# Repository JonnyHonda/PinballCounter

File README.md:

# Pinball Counter

An 8-digit decimal score counter built entirely from 74LS-series TTL logic.
Each digit has its own trigger input, so a pinball switch can add 1, 10, 100,
... directly. Digits carry into the next digit like electromechanical score
reels: when a digit goes 9 → 0, it adds 1 to the digit on its left.

## Files

| File | What it is |
|---|---|
| `PinballCounter.sch` | Autodesk EAGLE 9.x schematic (3 sheets, embedded library `pinball_ttl`) |
| `PinballCounter.brd` | EAGLE 9.x board: parts placed, connections as airwires, not yet routed |
| `gen_schematic.py` | Python 3 script that generates the schematic. Edit this, then rerun it; don't hand-edit the `.sch` file if you want to keep regenerating it. |
| `gen_board.py` | Generates the board from the same part and net data, so the schematic and board stay consistent |

Regenerate both with:

```sh
python3 gen_schematic.py && python3 gen_board.py
```

> Once you start routing in EAGLE, the `.brd` file holds your work, so
> rerunning `gen_board.py` would overwrite it. After that point, make
> changes in EAGLE.

The script runs a self-check (every symbol pin maps to a pad, no pad is used
twice, no net has only one connection). It prints any problems before writing
the file.

> **Status:** the schematic has not yet been opened in EAGLE. It parses as
> valid XML and passes the script's self-check, and rendered previews show a
> clean layout. The first step in EAGLE should be an ERC run (see *Known
> ERC warnings*).

## How it works

Signal path for each digit *n* (digit 1 = ones, digit 8 = ten-millions):

```
 Switch ──► 74LS221 one-shot ──► TRIGn ─┐
 (to GND)   (~23 ms, active low)        ├─► 74LS08 AND ─► CLKn ─► CPU  74LS192  Q0-Q3 ─► 74LS47 ─► 330R ×7 ─► 7-seg (CA)
 CARRY(n-1) from digit n-1 ─────────────┘                               /TCU ─► CARRYn (to digit n+1)
```

- **Debounce:** pinball switches bounce. Each input drives the falling-edge
  trigger (`/A`) of a non-retriggerable 74LS221 one-shot. Each one-shot outputs
  a single clean low pulse of width ≈ 0.7 × R × C = 0.7 × 33 kΩ × 1 µF ≈ 23 ms.
- **Trigger and carry merge:** the 74LS192 counts up on the *rising* edge of
  `CPU`. Its carry output `/TCU` is normally HIGH and goes LOW only when the
  count is 9 and `CPU` is low. When `CPU` rises, the counter goes to 0 and
  `/TCU` rises with it. The trigger and the carry both idle HIGH and pulse
  LOW, so ANDing them means either one pulls the clock low, and the return to
  HIGH counts one step.
- **Digit 1** has no carry in, so its AND input B is tied to VCC.
- **Display:** a 74LS47 (open-collector BCD → 7-segment decoder) drives a
  common-anode display through 330 Ω resistors, at about 9 mA per segment.
  There's no multiplexing; every digit is driven continuously.
- **Leading-zero blanking:** digit 8 `/RBI` = GND. Each digit's `/BI/RBO`
  feeds the `/RBI` of the digit below it, and digit 1 `/RBI` = VCC. A score
  of 0 therefore shows a single "0", and 1234 shows as `    1234`.
- **Reset:** the S1 pushbutton (to GND) and a 10 µF / 4.7 kΩ RC give a
  manual reset and a power-on reset. A 74LS14 Schmitt inverter turns this
  into an active-high `RESET` that drives `MR` on all eight 74LS192s.
  (Driving eight LS inputs from a gate avoids needing a very small pull-down
  resistor.)

## Schematic sheets

1. **Inputs, debounce, reset, power:** J1, J2, U19–U22 (74LS221), R1–R16,
   C1–C8, S1, R73, C9, U23 (74LS14), decoupling C10–C33.
2. **Counter chain:** U1–U8 (74LS192, one per digit) and U17–U18 (74LS08).
3. **Decoders and displays:** U9–U16 (74LS47), R17–R72 (segment resistors),
   DS1–DS8.

Connections use short wire stubs with **net labels**. Pins with the same
label are connected, including across sheets.

### Net naming

| Net | Meaning |
|---|---|
| `SWn` | Raw switch input n (J1 pin n, with pull-up) |
| `CXn`, `RCXn` | 74LS221 timing capacitor/resistor nodes for channel n |
| `TRIGn` | Debounced trigger pulse for digit n (active low) |
| `CARRYn` | 74LS192 `/TCU` of digit n → AND gate of digit n+1 |
| `CLKn` | Clock into `CPU` of digit n |
| `Dn_Q0`–`Dn_Q3` | BCD output of digit n |
| `Dn_SEGA`–`G` | 74LS47 output (before resistor) |
| `Dn_LEDA`–`G` | Display segment (after resistor) |
| `RBOn` | Blanking output of digit n → `/RBI` of digit n-1 |
| `RST_N`, `RESET` | Reset button node (active low) / buffered reset (active high) |

## Bill of materials

| Ref | Qty | Part | Notes |
|---|---|---|---|
| U1–U8 | 8 | 74LS192 | BCD up/down counter, DIP-16 |
| U9–U16 | 8 | 74LS47 | BCD → 7-seg decoder/driver, open collector, DIP-16 |
| U17–U18 | 2 | 74LS08 | Quad 2-input AND, DIP-14 |
| U19–U22 | 4 | 74LS221 | Dual monostable, DIP-16 |
| U23 | 1 | 74LS14 | Hex Schmitt inverter, DIP-14 |
| DS1–DS8 | 8 | 0.56" common-anode 7-seg | 5161BS / SA56-11 pinout |
| R1–R8 | 8 | 4.7 kΩ | Switch pull-ups |
| R9–R16 | 8 | 33 kΩ | One-shot timing |
| R17–R72 | 56 | 330 Ω | Segment current limiting |
| R73 | 1 | 4.7 kΩ | Reset pull-up |
| C1–C8 | 8 | 1 µF ceramic | One-shot timing (non-polarised) |
| C9 | 1 | 10 µF electrolytic | Power-on reset, pin 1 = + |
| C10–C32 | 23 | 100 nF ceramic | Decoupling, one per IC |
| C33 | 1 | 100 µF electrolytic | Bulk supply, pin 1 = + |
| S1 | 1 | 6 mm tactile switch | Reset |
| J1 | 1 | 1×10 header | SW1–SW8, GND, GND |
| J2 | 1 | 1×2 header | +5 V, GND |

**Power:** 5 V regulated, at least 1 A. All segments lit draws about 600 mA
for the LEDs plus about 300 mA for the logic.

## Board layout

**Size:** 194.9 × 160 mm, 2 layers, 4 × M3 mounting holes (3.2 mm) in the
corners.

**Arrangement (top view):** one column per digit, with digit 8 on the left
so the score reads normally. Each column, from top to bottom:

1. 7-segment display (with a silkscreen label for its place value: 10 000 000 … 1)
2. Seven 330 Ω segment resistors
3. 74LS47 decoder, then its 100 nF decoupling capacitor
4. 74LS192 counter

The lower part of the board holds the shared logic, from top to bottom:

- **74LS08 row:** two 74LS08s. U18 serves digits 5–8 and U17 serves digits
  1–4.
- **74LS221 row:** four 74LS221s, each under the two digits it serves.
- **R/C row:** each digit's pull-up, timing resistor and timing capacitor,
  standing vertically under its 74LS221.
- **Bottom edge:** J2 (+5 V / GND), C33 bulk capacitor, S1 reset, R73, C9,
  U23 (74LS14) and J1 (switch inputs, labelled SW1–SW8 / GND on the
  silkscreen).

**Details**
- All DIP chips use 0.3" footprints with a square pin-1 pad and a notch
  marking. Chips in the digit columns are rotated so pin 1 is at the top
  left.
- Each IC has its own 100 nF capacitor placed next to it.
- The segment resistors are stacked in the same order as the 74LS47 output
  pins (f, g, a, b, c, d, e, from bottom to top), so their tracks fan out
  without crossing.
- **Net classes:** `default` is 0.3 mm (12 mil) and `power` is 0.81 mm
  (32 mil). The power class covers VCC and GND.
- **GND** is a copper pour on the bottom layer, covering the whole board.

**Routing (to do in EAGLE)**
1. Open `PinballCounter.sch`. The board opens with it, and forward/back
   annotation should report the two files as consistent.
2. In the board, press **Ratsnest** to calculate the GND pour.
3. Route **VCC** first, by hand or with the autorouter limited to VCC. Use
   wide traces, ideally a tree from J2 running along each IC column.
4. Run **AUTO** for everything else, with 2 layers, a 0.3 mm track width,
   and the default via size.
5. Run **DRC** and fix any violations.

> **EAGLE edition:** this board is about 312 cm², which is larger than the
> EAGLE Free limit of 80 cm². Routing it needs a paid edition.

## Chip pinouts used (DIP)

**74LS192:** 1 P1 · 2 Q1 · 3 Q0 · 4 CPD · 5 CPU · 6 Q2 · 7 Q3 · 8 GND ·
9 P3 · 10 P2 · 11 /PL · 12 /TCU · 13 /TCD · 14 MR · 15 P0 · 16 VCC

- CPU = CLKn
- CPD and /PL = VCC
- P0–P3 = GND
- MR = RESET
- /TCD is unused

**74LS47:** 1 B · 2 C · 3 /LT · 4 /BI/RBO · 5 /RBI · 6 D · 7 A · 8 GND ·
9 e · 10 d · 11 c · 12 b · 13 a · 14 g · 15 f · 16 VCC

- /LT = VCC

**74LS08:** gate g (1–4) of U17 serves digit g, and gate g of U18 serves
digit 4+g. Input A = TRIG, input B = CARRY of the previous digit, output
Y = CLK.

**74LS221:** 1 /1A · 2 1B · 3 /1CLR · 4 /1Q · 5 2Q · 6 2Cext · 7 2Rext/Cext ·
8 GND · 9 /2A · 10 2B · 11 /2CLR · 12 /2Q · 13 1Q · 14 1Cext ·
15 1Rext/Cext · 16 VCC

- B and /CLR = VCC
- Q outputs are unused
- U19 serves digits 1–2, U20 digits 3–4, U21 digits 5–6, and U22 digits 7–8

**7-segment (5161BS):** 1 e · 2 d · 3 CA · 4 c · 5 dp · 6 b · 7 a · 8 CA ·
9 f · 10 g

## Known limitations

- **Simultaneous hits:** if a digit's own trigger overlaps an incoming carry
  pulse, the two LOW pulses merge and one count is lost. With ~23 ms pulses
  this is rare. Electromechanical machines behave the same way.
- **Minimum time between hits** on the same input is about the one-shot pulse
  width (23 ms). Change R9–R16 / C1–C8 to adjust it. The 74LS221 needs Rext
  between 1.4 kΩ and 100 kΩ.
- **Overflow:** past 99,999,999 the counter wraps to 0. `/TCU` of U8 is
  unconnected and could drive an overflow LED.
- **Logic families:** don't mix 74HC with 74LS. If you substitute parts, use
  74HCT.

## Known ERC warnings (expected)

These pins are deliberately left unconnected:

- 74LS192 `/TCD` on all digits, and `/TCU` on U8
- 74LS221 `1Q` and `2Q`
- 74LS47 `/BI/RBO` on digits 1 and 2
- Display `DP` pins

## Possible next steps

- [ ] Open in EAGLE, run ERC, and fix any import issues
- [ ] Breadboard one or two digits to confirm the trigger/carry timing
- [ ] Add an overflow LED on U8 `/TCU`
- [x] Board placement (`.brd`)
- [ ] Route the board (EAGLE autorouter + DRC) and generate Gerbers
- [ ] Optional: a multiplexed display version to reduce the chip count

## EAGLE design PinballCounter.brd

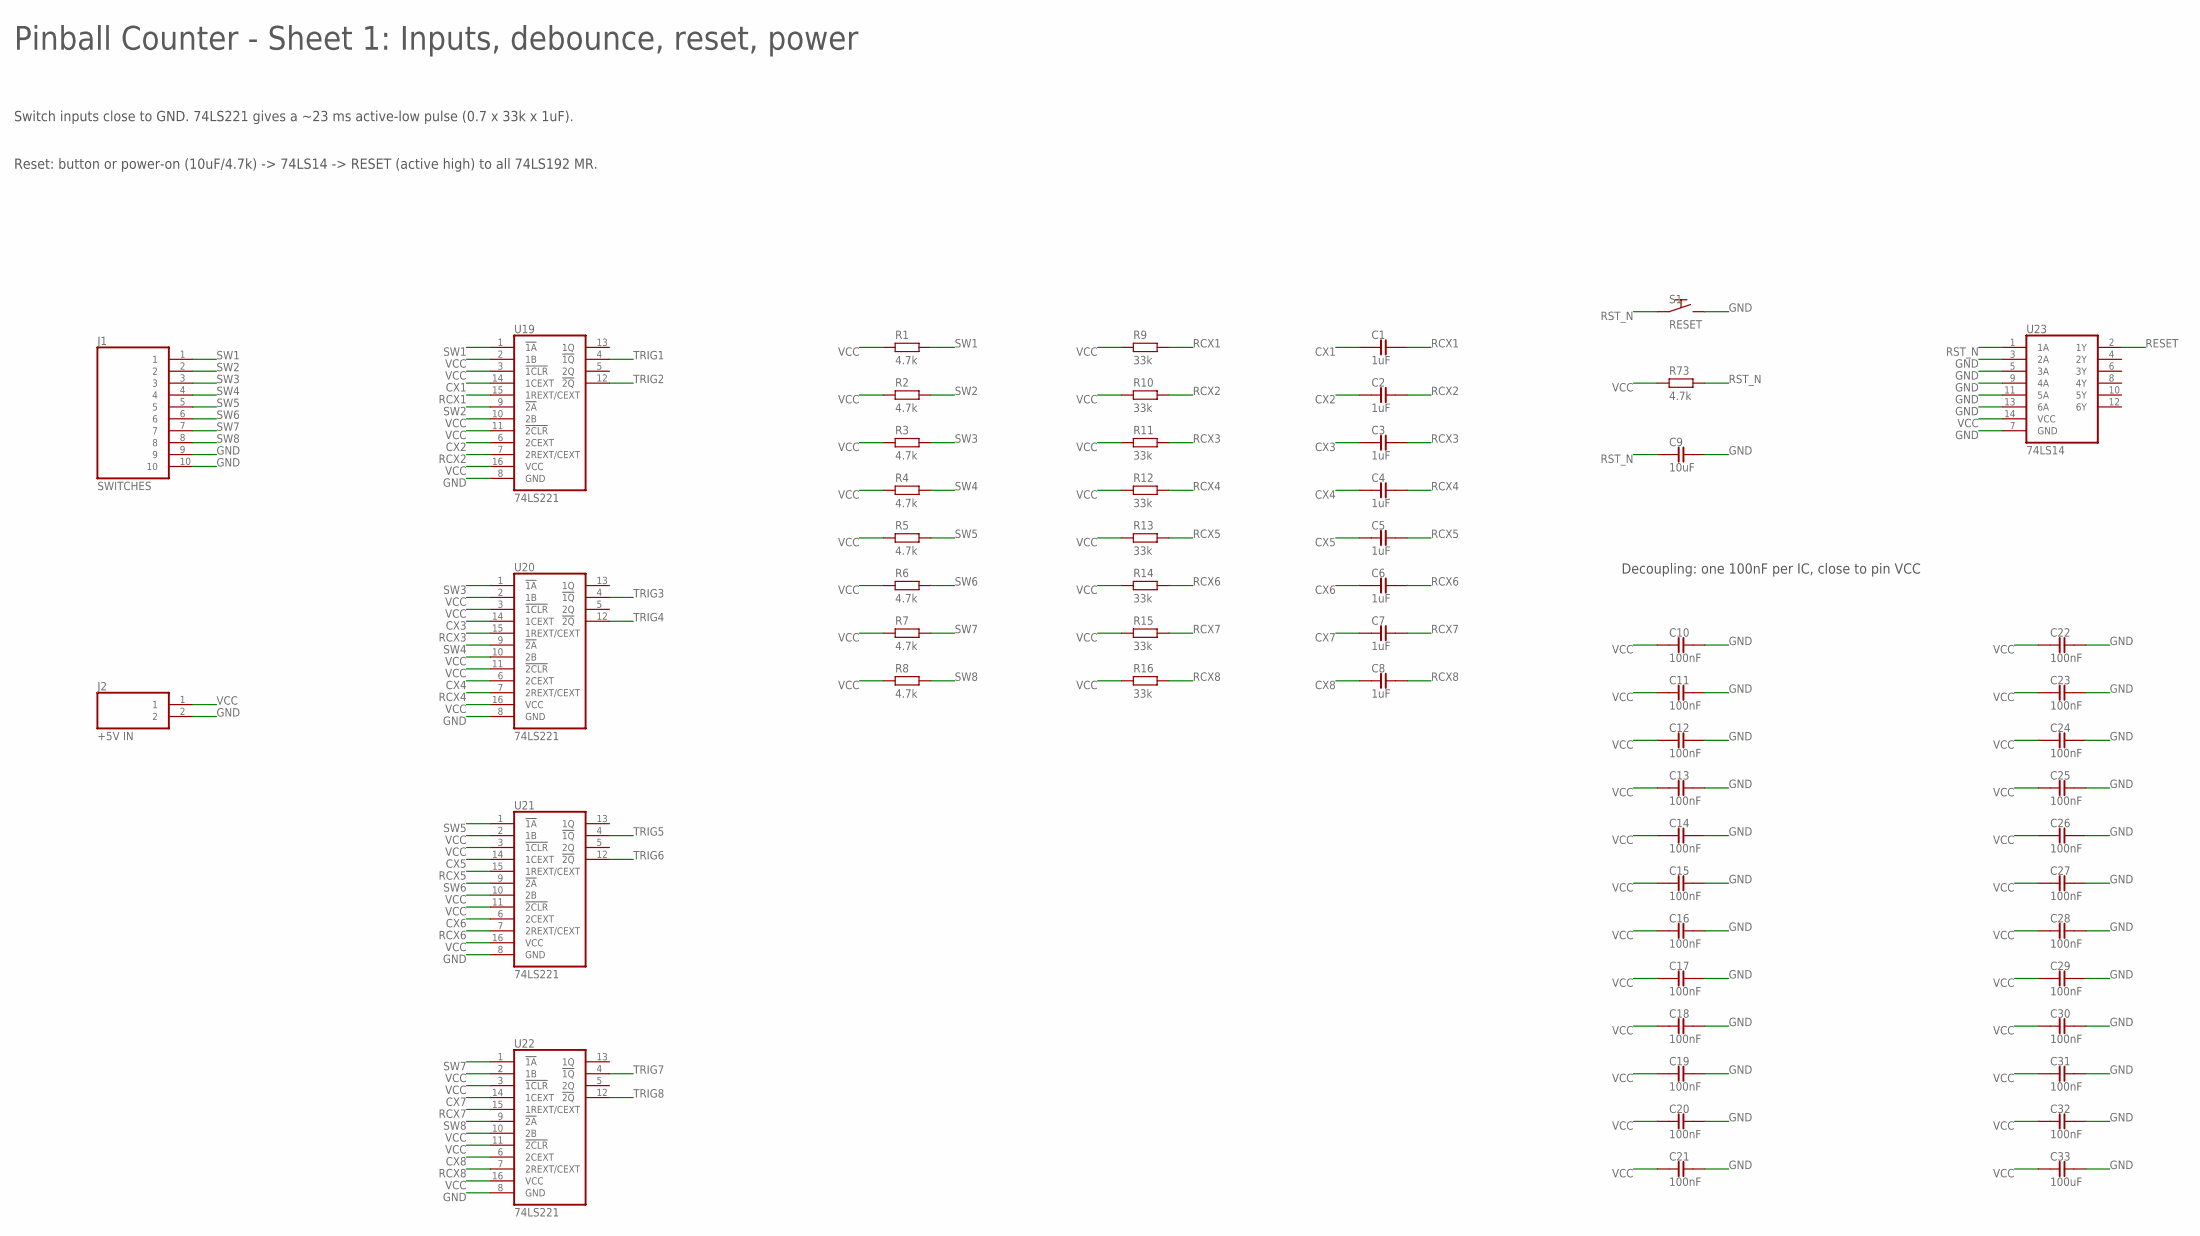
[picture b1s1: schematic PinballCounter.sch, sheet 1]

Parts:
C1, C2, C3, C4, C5, C6, C7, C8: 1uF; C2.5
C9: 10uF; E2.5-6
C10, C11, C12, C13, C14, C15, C16, C17, C18, C19, C20, C21, C22, C23, C24, C25, C26, C27, C28, C29, C30, C31, C32: 100nF; C2.5
C33: 100uF; E2.5-6
J1: SWITCHES; 1X10
J2: +5V IN; 1X02
R1, R2, R3, R4, R5, R6, R7, R8, R73: 4.7k; 0207/10
R9, R10, R11, R12, R13, R14, R15, R16: 33k; 0207/10
S1: RESET; TACT6MM
U19, U20, U21, U22: 74LS221; DIP16
U23: 74LS14; DIP14

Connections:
CX1: C1.1, U19.14 (1CEXT)
CX2: C2.1, U19.6 (2CEXT)
CX3: C3.1, U20.14 (1CEXT)
CX4: C4.1, U20.6 (2CEXT)
CX5: C5.1, U21.14 (1CEXT)
CX6: C6.1, U21.6 (2CEXT)
CX7: C7.1, U22.14 (1CEXT)
CX8: C8.1, U22.6 (2CEXT)
GND: C9.2, C10.2, C11.2, C12.2, C13.2, C14.2, C15.2, C16.2, C17.2, C18.2, C19.2, C20.2, C21.2, C22.2, C23.2, C24.2, C25.2, C26.2, C27.2, C28.2, C29.2, C30.2, C31.2, C32.2, C33.2, J1.9, J1.10, J2.2, S1.3 (2), S1.4 (2), U19.8 (GND), U20.8 (GND), U21.8 (GND), U22.8 (GND), U23.3 (2A), U23.5 (3A), U23.7 (GND), U23.9 (4A), U23.11 (5A), U23.13 (6A); also elsewhere on the board
RCX1: C1.2, R9.2, U19.15 (1REXT/CEXT)
RCX2: C2.2, R10.2, U19.7 (2REXT/CEXT)
RCX3: C3.2, R11.2, U20.15 (1REXT/CEXT)
RCX4: C4.2, R12.2, U20.7 (2REXT/CEXT)
RCX5: C5.2, R13.2, U21.15 (1REXT/CEXT)
RCX6: C6.2, R14.2, U21.7 (2REXT/CEXT)
RCX7: C7.2, R15.2, U22.15 (1REXT/CEXT)
RCX8: C8.2, R16.2, U22.7 (2REXT/CEXT)
RESET: U23.2 (1Y); also elsewhere on the board
RST_N: C9.1, R73.2, S1.1, S1.2 (1), U23.1 (1A)
SW1: J1.1, R1.2, U19.1 (!1A)
SW2: J1.2, R2.2, U19.9 (!2A)
SW3: J1.3, R3.2, U20.1 (!1A)
SW4: J1.4, R4.2, U20.9 (!2A)
SW5: J1.5, R5.2, U21.1 (!1A)
SW6: J1.6, R6.2, U21.9 (!2A)
SW7: J1.7, R7.2, U22.1 (!1A)
SW8: J1.8, R8.2, U22.9 (!2A)
TRIG1: U19.4 (!1Q); also elsewhere on the board
TRIG2: U19.12 (!2Q); also elsewhere on the board
TRIG3: U20.4 (!1Q); also elsewhere on the board
TRIG4: U20.12 (!2Q); also elsewhere on the board
TRIG5: U21.4 (!1Q); also elsewhere on the board
TRIG6: U21.12 (!2Q); also elsewhere on the board
TRIG7: U22.4 (!1Q); also elsewhere on the board
TRIG8: U22.12 (!2Q); also elsewhere on the board
VCC: C10.1, C11.1, C12.1, C13.1, C14.1, C15.1, C16.1, C17.1, C18.1, C19.1, C20.1, C21.1, C22.1, C23.1, C24.1, C25.1, C26.1, C27.1, C28.1, C29.1, C30.1, C31.1, C32.1, C33.1, J2.1, R1.1, R2.1, R3.1, R4.1, R5.1, R6.1, R7.1, R8.1, R9.1, R10.1, R11.1, R12.1, R13.1, R14.1, R15.1, R16.1, R73.1, U19.2 (1B), U19.3 (!1CLR), U19.10 (2B), U19.11 (!2CLR), U19.16 (VCC), U20.2 (1B), U20.3 (!1CLR), U20.10 (2B), U20.11 (!2CLR), U20.16 (VCC), U21.2 (1B), U21.3 (!1CLR), U21.10 (2B), U21.11 (!2CLR), U21.16 (VCC), U22.2 (1B), U22.3 (!1CLR), U22.10 (2B), U22.11 (!2CLR), U22.16 (VCC), U23.14 (VCC); also elsewhere on the board

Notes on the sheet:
Pinball Counter - Sheet 1: Inputs, debounce, reset, power
Switch inputs close to GND. 74LS221 gives a ~23 ms active-low pulse (0.7 x 33k x 1uF).
Reset: button or power-on (10uF/4.7k) -> 74LS14 -> RESET (active high) to all 74LS192 MR.
Decoupling: one 100nF per IC, close to pin VCC

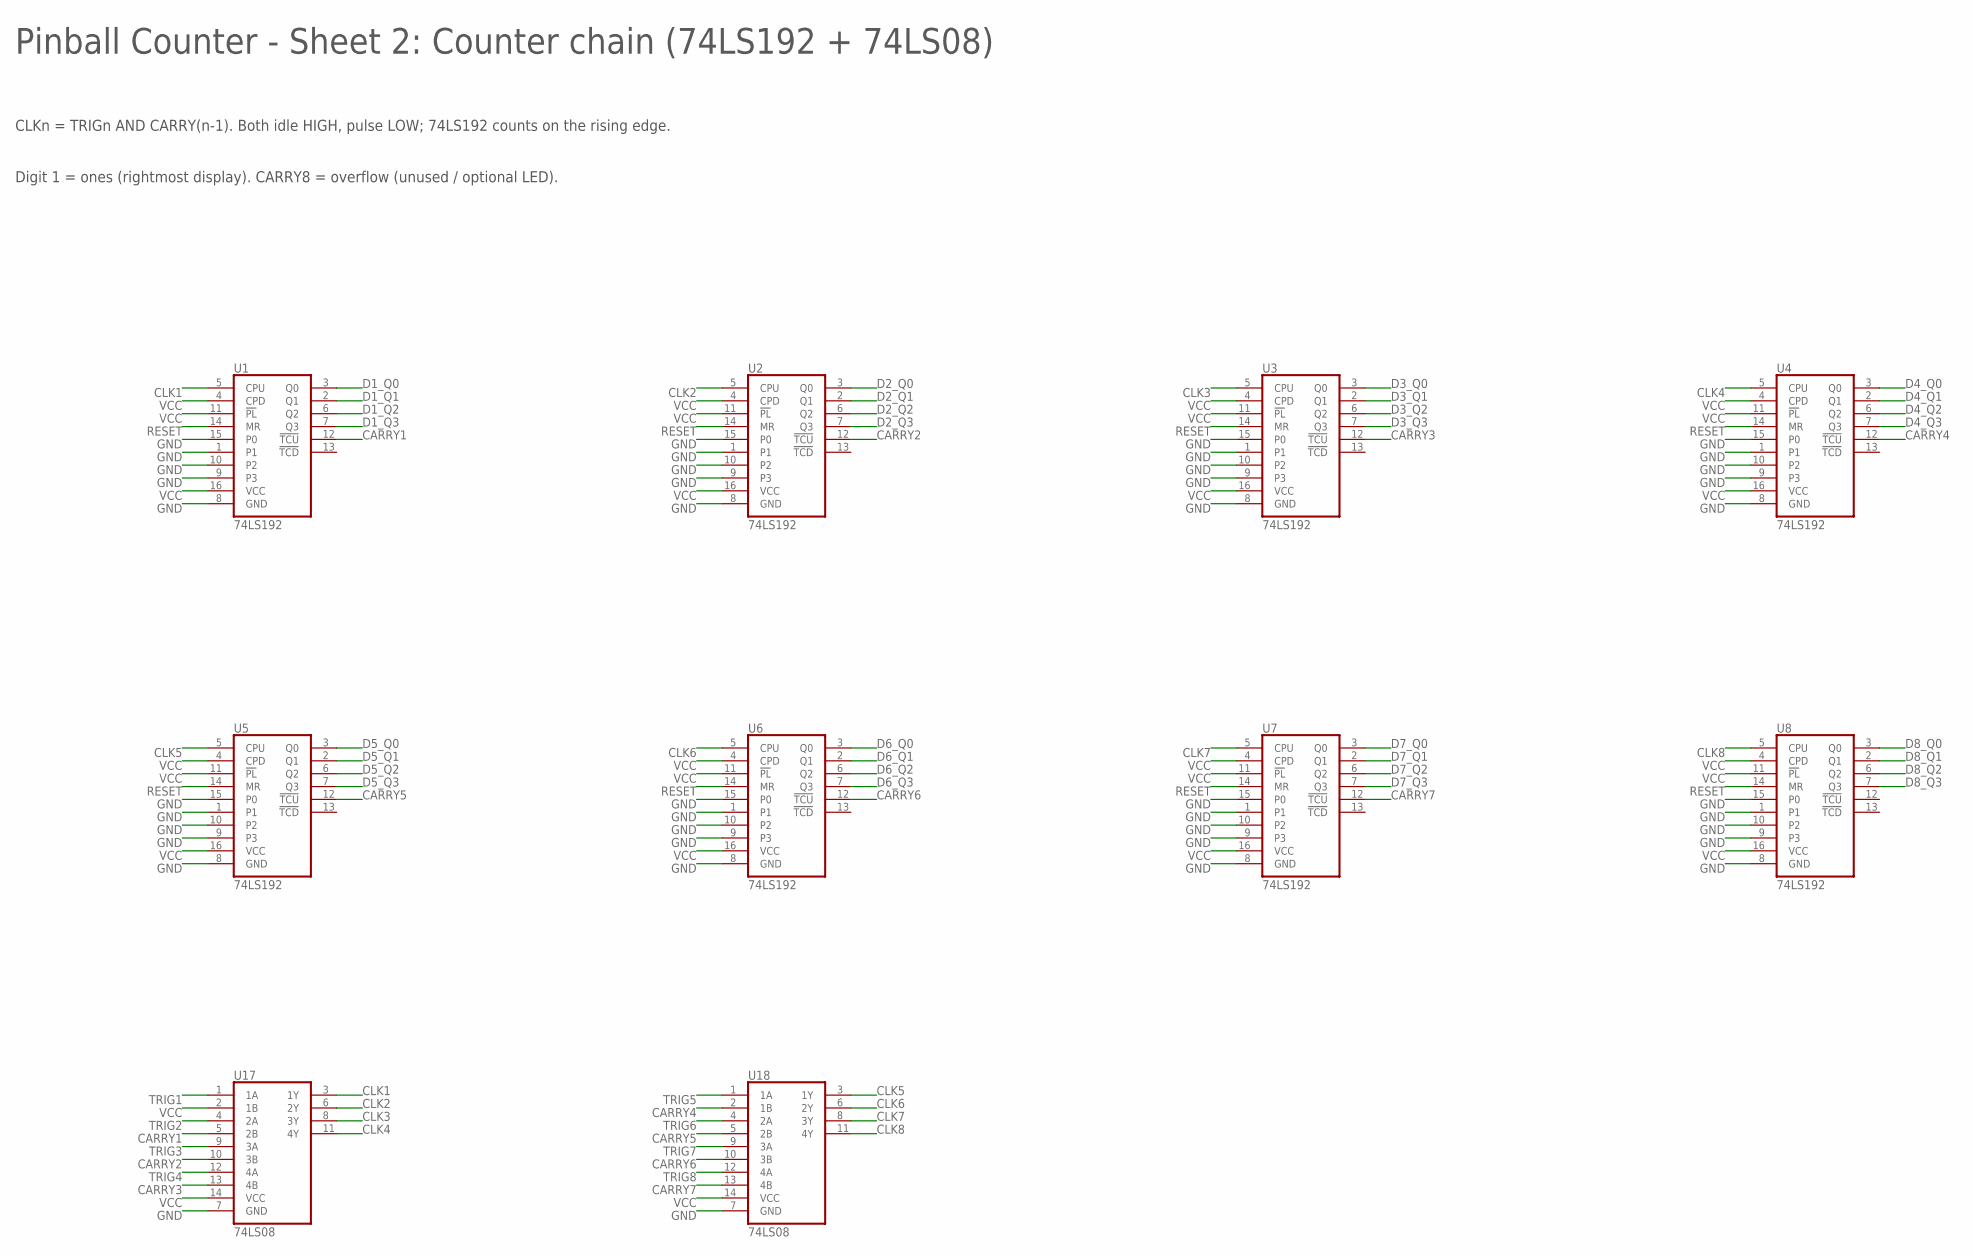
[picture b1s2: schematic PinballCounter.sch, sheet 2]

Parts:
U1, U2, U3, U4, U5, U6, U7, U8: 74LS192; DIP16
U17, U18: 74LS08; DIP14

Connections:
CARRY1: U1.12 (!TCU), U17.5 (2B)
CARRY2: U2.12 (!TCU), U17.10 (3B)
CARRY3: U3.12 (!TCU), U17.13 (4B)
CARRY4: U4.12 (!TCU), U18.2 (1B)
CARRY5: U5.12 (!TCU), U18.5 (2B)
CARRY6: U6.12 (!TCU), U18.10 (3B)
CARRY7: U7.12 (!TCU), U18.13 (4B)
CLK1: U1.5 (CPU), U17.3 (1Y)
CLK2: U2.5 (CPU), U17.6 (2Y)
CLK3: U3.5 (CPU), U17.8 (3Y)
CLK4: U4.5 (CPU), U17.11 (4Y)
CLK5: U5.5 (CPU), U18.3 (1Y)
CLK6: U6.5 (CPU), U18.6 (2Y)
CLK7: U7.5 (CPU), U18.8 (3Y)
CLK8: U8.5 (CPU), U18.11 (4Y)
D1_Q0: U1.3 (Q0); also elsewhere on the board
D1_Q1: U1.2 (Q1); also elsewhere on the board
D1_Q2: U1.6 (Q2); also elsewhere on the board
D1_Q3: U1.7 (Q3); also elsewhere on the board
D2_Q0: U2.3 (Q0); also elsewhere on the board
D2_Q1: U2.2 (Q1); also elsewhere on the board
D2_Q2: U2.6 (Q2); also elsewhere on the board
D2_Q3: U2.7 (Q3); also elsewhere on the board
D3_Q0: U3.3 (Q0); also elsewhere on the board
D3_Q1: U3.2 (Q1); also elsewhere on the board
D3_Q2: U3.6 (Q2); also elsewhere on the board
D3_Q3: U3.7 (Q3); also elsewhere on the board
D4_Q0: U4.3 (Q0); also elsewhere on the board
D4_Q1: U4.2 (Q1); also elsewhere on the board
D4_Q2: U4.6 (Q2); also elsewhere on the board
D4_Q3: U4.7 (Q3); also elsewhere on the board
D5_Q0: U5.3 (Q0); also elsewhere on the board
D5_Q1: U5.2 (Q1); also elsewhere on the board
D5_Q2: U5.6 (Q2); also elsewhere on the board
D5_Q3: U5.7 (Q3); also elsewhere on the board
D6_Q0: U6.3 (Q0); also elsewhere on the board
D6_Q1: U6.2 (Q1); also elsewhere on the board
D6_Q2: U6.6 (Q2); also elsewhere on the board
D6_Q3: U6.7 (Q3); also elsewhere on the board
D7_Q0: U7.3 (Q0); also elsewhere on the board
D7_Q1: U7.2 (Q1); also elsewhere on the board
D7_Q2: U7.6 (Q2); also elsewhere on the board
D7_Q3: U7.7 (Q3); also elsewhere on the board
D8_Q0: U8.3 (Q0); also elsewhere on the board
D8_Q1: U8.2 (Q1); also elsewhere on the board
D8_Q2: U8.6 (Q2); also elsewhere on the board
D8_Q3: U8.7 (Q3); also elsewhere on the board
GND: U1.1, U1.8 (GND), U1.9 (P3), U1.10 (P2), U1.15 (P0), U2.1, U2.8 (GND), U2.9 (P3), U2.10 (P2), U2.15 (P0), U3.1, U3.8 (GND), U3.9 (P3), U3.10 (P2), U3.15 (P0), U4.1, U4.8 (GND), U4.9 (P3), U4.10 (P2), U4.15 (P0), U5.1, U5.8 (GND), U5.9 (P3), U5.10 (P2), U5.15 (P0), U6.1, U6.8 (GND), U6.9 (P3), U6.10 (P2), U6.15 (P0), U7.1, U7.8 (GND), U7.9 (P3), U7.10 (P2), U7.15 (P0), U8.1, U8.8 (GND), U8.9 (P3), U8.10 (P2), U8.15 (P0), U17.7 (GND), U18.7 (GND); also elsewhere on the board
RESET: U1.14 (MR), U2.14 (MR), U3.14 (MR), U4.14 (MR), U5.14 (MR), U6.14 (MR), U7.14 (MR), U8.14 (MR); also elsewhere on the board
TRIG1: U17.1 (1A); also elsewhere on the board
TRIG2: U17.4 (2A); also elsewhere on the board
TRIG3: U17.9 (3A); also elsewhere on the board
TRIG4: U17.12 (4A); also elsewhere on the board
TRIG5: U18.1 (1A); also elsewhere on the board
TRIG6: U18.4 (2A); also elsewhere on the board
TRIG7: U18.9 (3A); also elsewhere on the board
TRIG8: U18.12 (4A); also elsewhere on the board
VCC: U1.4 (CPD), U1.11 (!PL), U1.16 (VCC), U2.4 (CPD), U2.11 (!PL), U2.16 (VCC), U3.4 (CPD), U3.11 (!PL), U3.16 (VCC), U4.4 (CPD), U4.11 (!PL), U4.16 (VCC), U5.4 (CPD), U5.11 (!PL), U5.16 (VCC), U6.4 (CPD), U6.11 (!PL), U6.16 (VCC), U7.4 (CPD), U7.11 (!PL), U7.16 (VCC), U8.4 (CPD), U8.11 (!PL), U8.16 (VCC), U17.2 (1B), U17.14 (VCC), U18.14 (VCC); also elsewhere on the board

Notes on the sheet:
Pinball Counter - Sheet 2: Counter chain (74LS192 + 74LS08)
CLKn = TRIGn AND CARRY(n-1). Both idle HIGH, pulse LOW; 74LS192 counts on the rising edge.
Digit 1 = ones (rightmost display). CARRY8 = overflow (unused / optional LED).

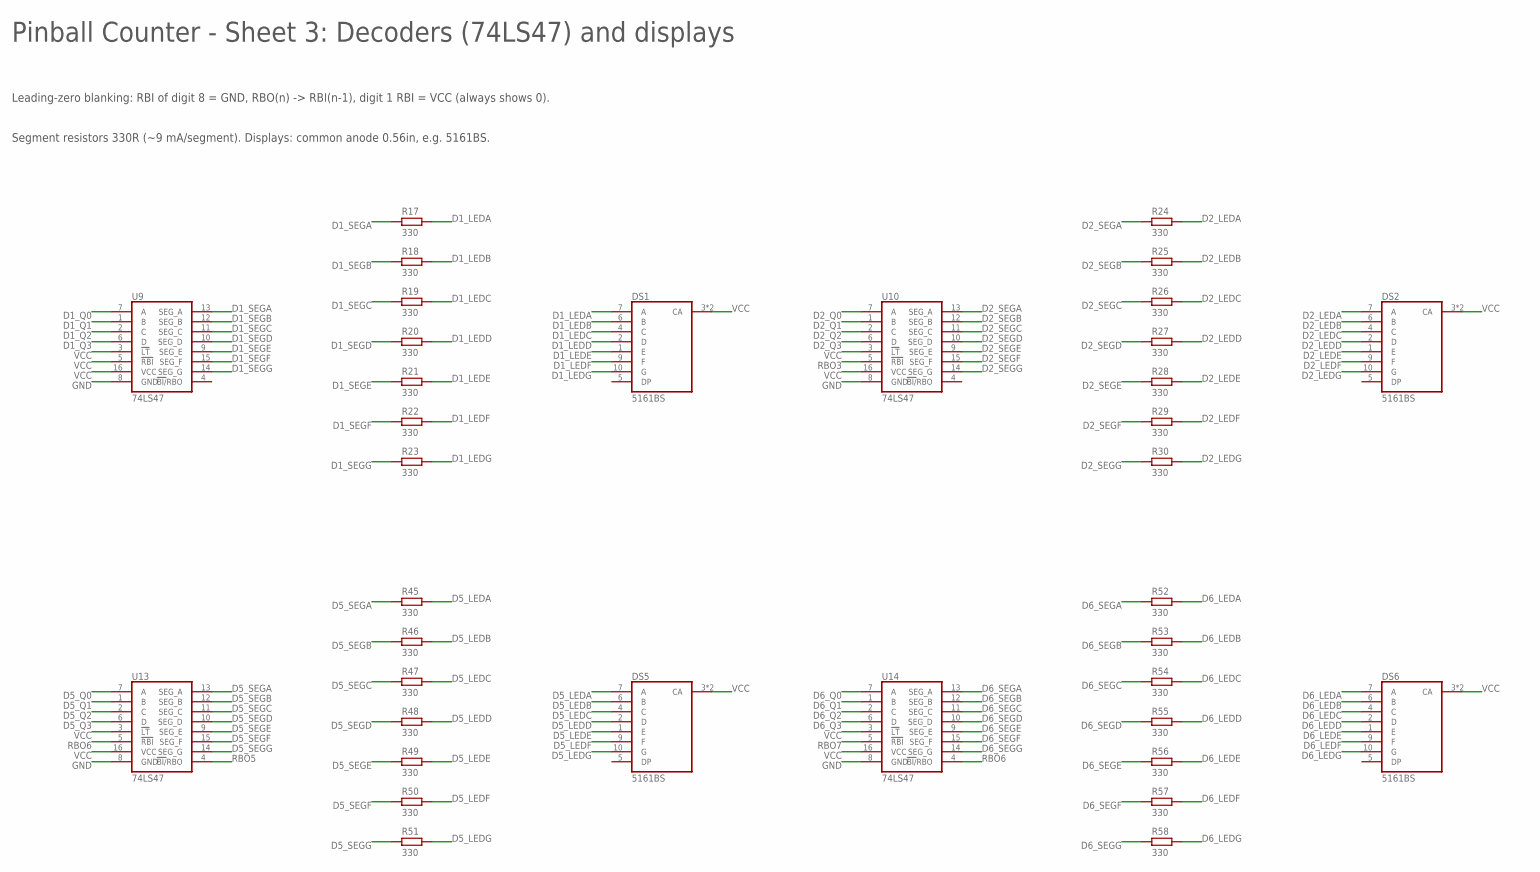
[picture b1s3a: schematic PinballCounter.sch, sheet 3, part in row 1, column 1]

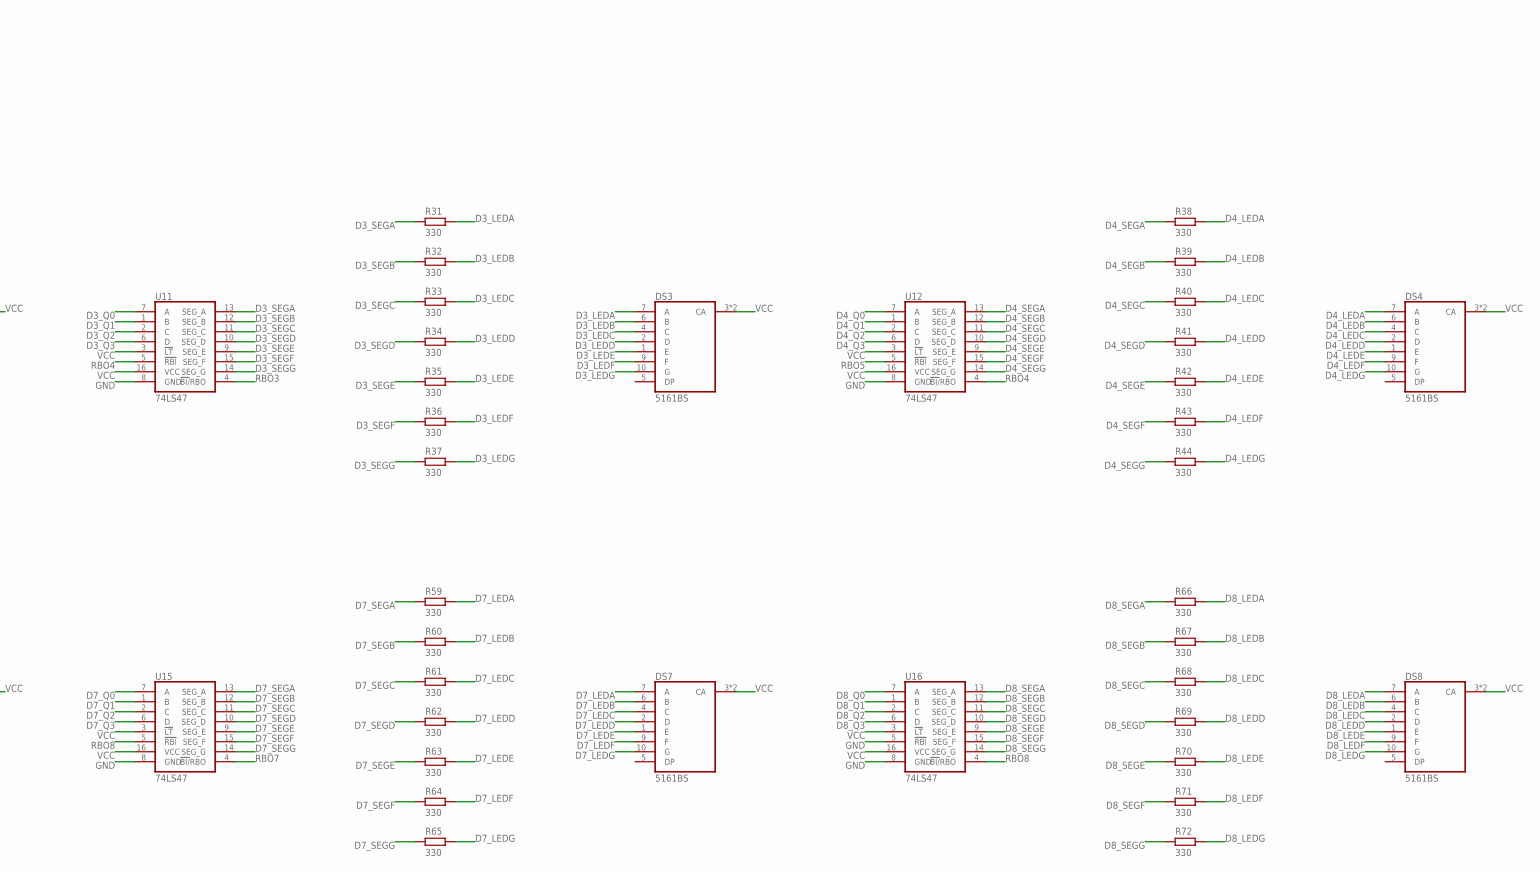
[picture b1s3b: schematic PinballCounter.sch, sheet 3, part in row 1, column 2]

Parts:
DS1, DS2, DS3, DS4, DS5, DS6, DS7, DS8: 5161BS; 7SEG-056
R17, R18, R19, R20, R21, R22, R23, R24, R25, R26, R27, R28, R29, R30, R31, R32, R33, R34, R35, R36, R37, R38, R39, R40, R41, R42, R43, R44, R45, R46, R47, R48, R49, R50, R51, R52, R53, R54, R55, R56, R57, R58, R59, R60, R61, R62, R63, R64, R65, R66, R67, R68, R69, R70, R71, R72: 330; 0207/10
U9, U10, U11, U12, U13, U14, U15, U16: 74LS47; DIP16

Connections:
D1_LEDA: DS1.7 (A), R17.2
D1_LEDB: DS1.6 (B), R18.2
D1_LEDC: DS1.4 (C), R19.2
D1_LEDD: DS1.2 (D), R20.2
D1_LEDE: DS1.1 (E), R21.2
D1_LEDF: DS1.9 (F), R22.2
D1_LEDG: DS1.10 (G), R23.2
D1_Q0: U9.7 (A); also elsewhere on the board
D1_Q1: U9.1 (B); also elsewhere on the board
D1_Q2: U9.2 (C); also elsewhere on the board
D1_Q3: U9.6 (D); also elsewhere on the board
D1_SEGA: R17.1, U9.13 (SEG_A)
D1_SEGB: R18.1, U9.12 (SEG_B)
D1_SEGC: R19.1, U9.11 (SEG_C)
D1_SEGD: R20.1, U9.10 (SEG_D)
D1_SEGE: R21.1, U9.9 (SEG_E)
D1_SEGF: R22.1, U9.15 (SEG_F)
D1_SEGG: R23.1, U9.14 (SEG_G)
D2_LEDA: DS2.7 (A), R24.2
D2_LEDB: DS2.6 (B), R25.2
D2_LEDC: DS2.4 (C), R26.2
D2_LEDD: DS2.2 (D), R27.2
D2_LEDE: DS2.1 (E), R28.2
D2_LEDF: DS2.9 (F), R29.2
D2_LEDG: DS2.10 (G), R30.2
D2_Q0: U10.7 (A); also elsewhere on the board
D2_Q1: U10.1 (B); also elsewhere on the board
D2_Q2: U10.2 (C); also elsewhere on the board
D2_Q3: U10.6 (D); also elsewhere on the board
D2_SEGA: R24.1, U10.13 (SEG_A)
D2_SEGB: R25.1, U10.12 (SEG_B)
D2_SEGC: R26.1, U10.11 (SEG_C)
D2_SEGD: R27.1, U10.10 (SEG_D)
D2_SEGE: R28.1, U10.9 (SEG_E)
D2_SEGF: R29.1, U10.15 (SEG_F)
D2_SEGG: R30.1, U10.14 (SEG_G)
D3_LEDA: DS3.7 (A), R31.2
D3_LEDB: DS3.6 (B), R32.2
D3_LEDC: DS3.4 (C), R33.2
D3_LEDD: DS3.2 (D), R34.2
D3_LEDE: DS3.1 (E), R35.2
D3_LEDF: DS3.9 (F), R36.2
D3_LEDG: DS3.10 (G), R37.2
D3_Q0: U11.7 (A); also elsewhere on the board
D3_Q1: U11.1 (B); also elsewhere on the board
D3_Q2: U11.2 (C); also elsewhere on the board
D3_Q3: U11.6 (D); also elsewhere on the board
D3_SEGA: R31.1, U11.13 (SEG_A)
D3_SEGB: R32.1, U11.12 (SEG_B)
D3_SEGC: R33.1, U11.11 (SEG_C)
D3_SEGD: R34.1, U11.10 (SEG_D)
D3_SEGE: R35.1, U11.9 (SEG_E)
D3_SEGF: R36.1, U11.15 (SEG_F)
D3_SEGG: R37.1, U11.14 (SEG_G)
D4_LEDA: DS4.7 (A), R38.2
D4_LEDB: DS4.6 (B), R39.2
D4_LEDC: DS4.4 (C), R40.2
D4_LEDD: DS4.2 (D), R41.2
D4_LEDE: DS4.1 (E), R42.2
D4_LEDF: DS4.9 (F), R43.2
D4_LEDG: DS4.10 (G), R44.2
D4_Q0: U12.7 (A); also elsewhere on the board
D4_Q1: U12.1 (B); also elsewhere on the board
D4_Q2: U12.2 (C); also elsewhere on the board
D4_Q3: U12.6 (D); also elsewhere on the board
D4_SEGA: R38.1, U12.13 (SEG_A)
D4_SEGB: R39.1, U12.12 (SEG_B)
D4_SEGC: R40.1, U12.11 (SEG_C)
D4_SEGD: R41.1, U12.10 (SEG_D)
D4_SEGE: R42.1, U12.9 (SEG_E)
D4_SEGF: R43.1, U12.15 (SEG_F)
D4_SEGG: R44.1, U12.14 (SEG_G)
D5_LEDA: DS5.7 (A), R45.2
D5_LEDB: DS5.6 (B), R46.2
D5_LEDC: DS5.4 (C), R47.2
D5_LEDD: DS5.2 (D), R48.2
D5_LEDE: DS5.1 (E), R49.2
D5_LEDF: DS5.9 (F), R50.2
D5_LEDG: DS5.10 (G), R51.2
D5_Q0: U13.7 (A); also elsewhere on the board
D5_Q1: U13.1 (B); also elsewhere on the board
D5_Q2: U13.2 (C); also elsewhere on the board
D5_Q3: U13.6 (D); also elsewhere on the board
D5_SEGA: R45.1, U13.13 (SEG_A)
D5_SEGB: R46.1, U13.12 (SEG_B)
D5_SEGC: R47.1, U13.11 (SEG_C)
D5_SEGD: R48.1, U13.10 (SEG_D)
D5_SEGE: R49.1, U13.9 (SEG_E)
D5_SEGF: R50.1, U13.15 (SEG_F)
D5_SEGG: R51.1, U13.14 (SEG_G)
D6_LEDA: DS6.7 (A), R52.2
D6_LEDB: DS6.6 (B), R53.2
D6_LEDC: DS6.4 (C), R54.2
D6_LEDD: DS6.2 (D), R55.2
D6_LEDE: DS6.1 (E), R56.2
D6_LEDF: DS6.9 (F), R57.2
D6_LEDG: DS6.10 (G), R58.2
D6_Q0: U14.7 (A); also elsewhere on the board
D6_Q1: U14.1 (B); also elsewhere on the board
D6_Q2: U14.2 (C); also elsewhere on the board
D6_Q3: U14.6 (D); also elsewhere on the board
D6_SEGA: R52.1, U14.13 (SEG_A)
D6_SEGB: R53.1, U14.12 (SEG_B)
D6_SEGC: R54.1, U14.11 (SEG_C)
D6_SEGD: R55.1, U14.10 (SEG_D)
D6_SEGE: R56.1, U14.9 (SEG_E)
D6_SEGF: R57.1, U14.15 (SEG_F)
D6_SEGG: R58.1, U14.14 (SEG_G)
D7_LEDA: DS7.7 (A), R59.2
D7_LEDB: DS7.6 (B), R60.2
D7_LEDC: DS7.4 (C), R61.2
D7_LEDD: DS7.2 (D), R62.2
D7_LEDE: DS7.1 (E), R63.2
D7_LEDF: DS7.9 (F), R64.2
D7_LEDG: DS7.10 (G), R65.2
D7_Q0: U15.7 (A); also elsewhere on the board
D7_Q1: U15.1 (B); also elsewhere on the board
D7_Q2: U15.2 (C); also elsewhere on the board
D7_Q3: U15.6 (D); also elsewhere on the board
D7_SEGA: R59.1, U15.13 (SEG_A)
D7_SEGB: R60.1, U15.12 (SEG_B)
D7_SEGC: R61.1, U15.11 (SEG_C)
D7_SEGD: R62.1, U15.10 (SEG_D)
D7_SEGE: R63.1, U15.9 (SEG_E)
D7_SEGF: R64.1, U15.15 (SEG_F)
D7_SEGG: R65.1, U15.14 (SEG_G)
D8_LEDA: DS8.7 (A), R66.2
D8_LEDB: DS8.6 (B), R67.2
D8_LEDC: DS8.4 (C), R68.2
D8_LEDD: DS8.2 (D), R69.2
D8_LEDE: DS8.1 (E), R70.2
D8_LEDF: DS8.9 (F), R71.2
D8_LEDG: DS8.10 (G), R72.2
D8_Q0: U16.7 (A); also elsewhere on the board
D8_Q1: U16.1 (B); also elsewhere on the board
D8_Q2: U16.2 (C); also elsewhere on the board
D8_Q3: U16.6 (D); also elsewhere on the board
D8_SEGA: R66.1, U16.13 (SEG_A)
D8_SEGB: R67.1, U16.12 (SEG_B)
D8_SEGC: R68.1, U16.11 (SEG_C)
D8_SEGD: R69.1, U16.10 (SEG_D)
D8_SEGE: R70.1, U16.9 (SEG_E)
D8_SEGF: R71.1, U16.15 (SEG_F)
D8_SEGG: R72.1, U16.14 (SEG_G)
GND: U9.8 (GND), U10.8 (GND), U11.8 (GND), U12.8 (GND), U13.8 (GND), U14.8 (GND), U15.8 (GND), U16.5 (!RBI), U16.8 (GND); also elsewhere on the board
RBO3: U10.5 (!RBI), U11.4 (!BI/!RBO)
RBO4: U11.5 (!RBI), U12.4 (!BI/!RBO)
RBO5: U12.5 (!RBI), U13.4 (!BI/!RBO)
RBO6: U13.5 (!RBI), U14.4 (!BI/!RBO)
RBO7: U14.5 (!RBI), U15.4 (!BI/!RBO)
RBO8: U15.5 (!RBI), U16.4 (!BI/!RBO)
VCC: DS1.3 (CA), DS1.8 (CA), DS2.3 (CA), DS2.8 (CA), DS3.3 (CA), DS3.8 (CA), DS4.3 (CA), DS4.8 (CA), DS5.3 (CA), DS5.8 (CA), DS6.3 (CA), DS6.8 (CA), DS7.3 (CA), DS7.8 (CA), DS8.3 (CA), DS8.8 (CA), U9.3 (!LT), U9.5 (!RBI), U9.16 (VCC), U10.3 (!LT), U10.16 (VCC), U11.3 (!LT), U11.16 (VCC), U12.3 (!LT), U12.16 (VCC), U13.3 (!LT), U13.16 (VCC), U14.3 (!LT), U14.16 (VCC), U15.3 (!LT), U15.16 (VCC), U16.3 (!LT), U16.16 (VCC); also elsewhere on the board

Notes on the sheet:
Pinball Counter - Sheet 3: Decoders (74LS47) and displays
Leading-zero blanking: RBI of digit 8 = GND, RBO(n) -> RBI(n-1), digit 1 RBI = VCC (always shows 0).
Segment resistors 330R (~9 mA/segment). Displays: common anode 0.56in, e.g. 5161BS.

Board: 1 copper layer, 140 parts (0 on the bottom side), 201 nets, no tracks yet.
